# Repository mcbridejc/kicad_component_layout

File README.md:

# Kicad Component Layout Plugin

A python plugin for KiCad to assist with script driven component layout.

## How to install

The `component_layout_plugin.py` file needs to be located into the KiCad script search path. For
example, on linux, it could go in `~/.kicad/scripting`. In python 6.0.1 (and later?) you can go to
`Tools->External Plugins->Open Plugins Directory` to find the location.
Once there, the script should be available to run in KiCad under 'Tools -> External Pluging', or
using the button on the toolbar.

For Windows:

The Windows version of KiCad packages its own internal copy of Python 2.7. To install the required YAML dependency, open a command prompt as administrator and type:

```
"C:\Program Files\KiCad\bin\python.exe" -m pip install pyyaml==5.2
```

## How to use

When run in pcbnew, the plugin reads information about how to position components on the board from
the file `layout.yaml` located in the project directory. The data in layout yaml allows the plugin
to change the layer (top/bottom), position, rotation, and footprint for the given module.

An example layout.yaml file:

```
    origin: [x0, y0] # Offset applied to all component locations
    components:
        R1:
            location: [x, y] # mm
            rotation: r # degrees (float)
            flip: false
            footprint:
                path: path/to/library.pretty
                name: SomeFootprint
        J1:
            ...
```

All the fields are optional for each component (e.g. leave footprint unspecified
to leave the footprint unchanged).

The footprint path is relative to the directory containing the KiCad PCB file.

Typically, I will then create a python script to generate the layout.yaml based on the needs of
the design.

The components must be instantiated in the schematic first.

## Caveats

1. The schematic has to assign a footprint, so if you override the footprint in
layout.yaml, the plugin will have to be run again after importing changes from
schematic in order to restore the footprint.
2. You have to check the "Re-associate footprints by refdes" option when performing
the update from schematic. If you don't, it will delete and recreate all the
components with the footprints in the schematic. You can simply run the plugin again to fix them.
3. This works with KiCad 5.1.9, and with KiCad 6.0.4 -- see below for 6.0.1, and 6.0.2. It may stop working on a future version.
4. Make sure you do not have any components selected when you run the layout plugin.
If your layout file changes footprints while components are selected, this causes KiCad
to crash -- this appears to no longer be an issue in KiCad 6.x.

## Known issue with 6.0.1, 6.0.2

This script is updated to work with KiCad 6.0.1. There were some changes, and
if you have an old version it will not work -- likely you get will an error
about missing the 'FindModuleByReference` function. However, there is an unresolved
issue that causes KiCad to segfault on exit after the script is run. This doesn't
prevent the script from working, and as far as I can tell, KiCad continues to run
correctly after running the script until you exit.
See [this issue](https://gitlab.com/kicad/code/kicad/-/issues/10951).

This was resolved in 6.0.3.

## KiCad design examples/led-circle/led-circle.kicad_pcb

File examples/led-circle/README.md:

# LED Circle Layout Example

A Kicad project with an example script for generating layout.yaml to place a number of LEDs in a circle. 

## Steps to Create

Add LEDs to your design in eeschema, and wire them up as needed, and assign them an appropriate footprint. 

Open the PCB design in pcbnew, and draw the board outline: 

- Set the grid to a 1mm so that you can easily place the circle center on a nice even grid location (0.1" is fine, if you prefer those units)
- Draw a circle centered at coordinates (200, 80) -- actually it doesn't matter where, but I recommend a nice round number for ease -- with 15mm radius on the edge.cuts layer. This defines the shape of the board.
- Run "Update PCB from Schematic" to pull in your LED footprints, and place them anywhere. 
- Create the layout.py script, and run it to generate layout.yaml in the project directory
- Run the component layout plugin in pcbnew to read positions from layout.yaml and adjust your footprints.

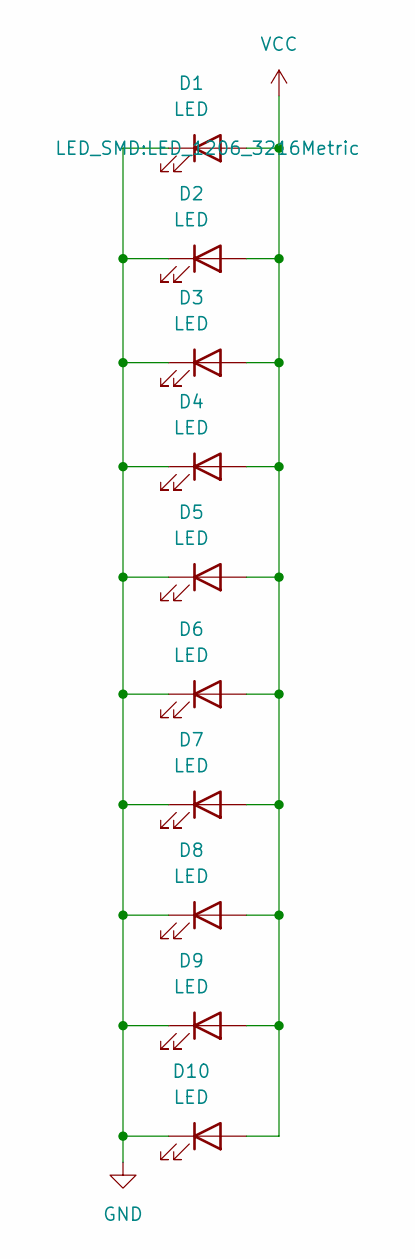
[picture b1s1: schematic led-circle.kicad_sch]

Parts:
D1, D2, D3, D4, D5, D6, D7, D8, D9, D10: LED; LED_1206_3216Metric

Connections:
GND: D1.1 (K), D2.1 (K), D3.1 (K), D4.1 (K), D5.1 (K), D6.1 (K), D7.1 (K), D8.1 (K), D9.1 (K), D10.1 (K)
VCC: D1.2 (A), D2.2 (A), D3.2 (A), D4.2 (A), D5.2 (A), D6.2 (A), D7.2 (A), D8.2 (A), D9.2 (A), D10.2 (A)

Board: 2 copper layers, 10 parts (10 on the bottom side), 2 nets, no tracks yet.

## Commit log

2021-03-12 Add some caveats
2021-12-17 Windows (py27) compatibility
2021-12-17 Added Windows install instructions
2022-02-23 Update to work with kicad 6*
    Also, fixes log level so that info messages actually get logged.
    *Some issue with segfault on close after running the script still persists: https://gitlab.com/kicad/code/kicad/-/issues/10951
2022-04-26 Update example YAML
    Rotation should be a scalar, not a list.
2022-04-26 Update version compatibility info
2022-06-24 Fix flipped
2022-06-24 Use props.get
2022-06-25 Correct 'flipped' to 'flip' in layout.yaml example
2022-07-22 Return 'flipped' attribute back to 'flip
2022-07-22 Add example project for laying out LEDs in a circle
2022-07-27 Handle version strings with parentheses
2022-08-04 feat: Component placement data can now be imported/exported to files selected by a file browser dialog.
2023-04-10 Fixed for KiCad 7
2024-03-21 improve kicad version checking for compatibility with kicad 7+
